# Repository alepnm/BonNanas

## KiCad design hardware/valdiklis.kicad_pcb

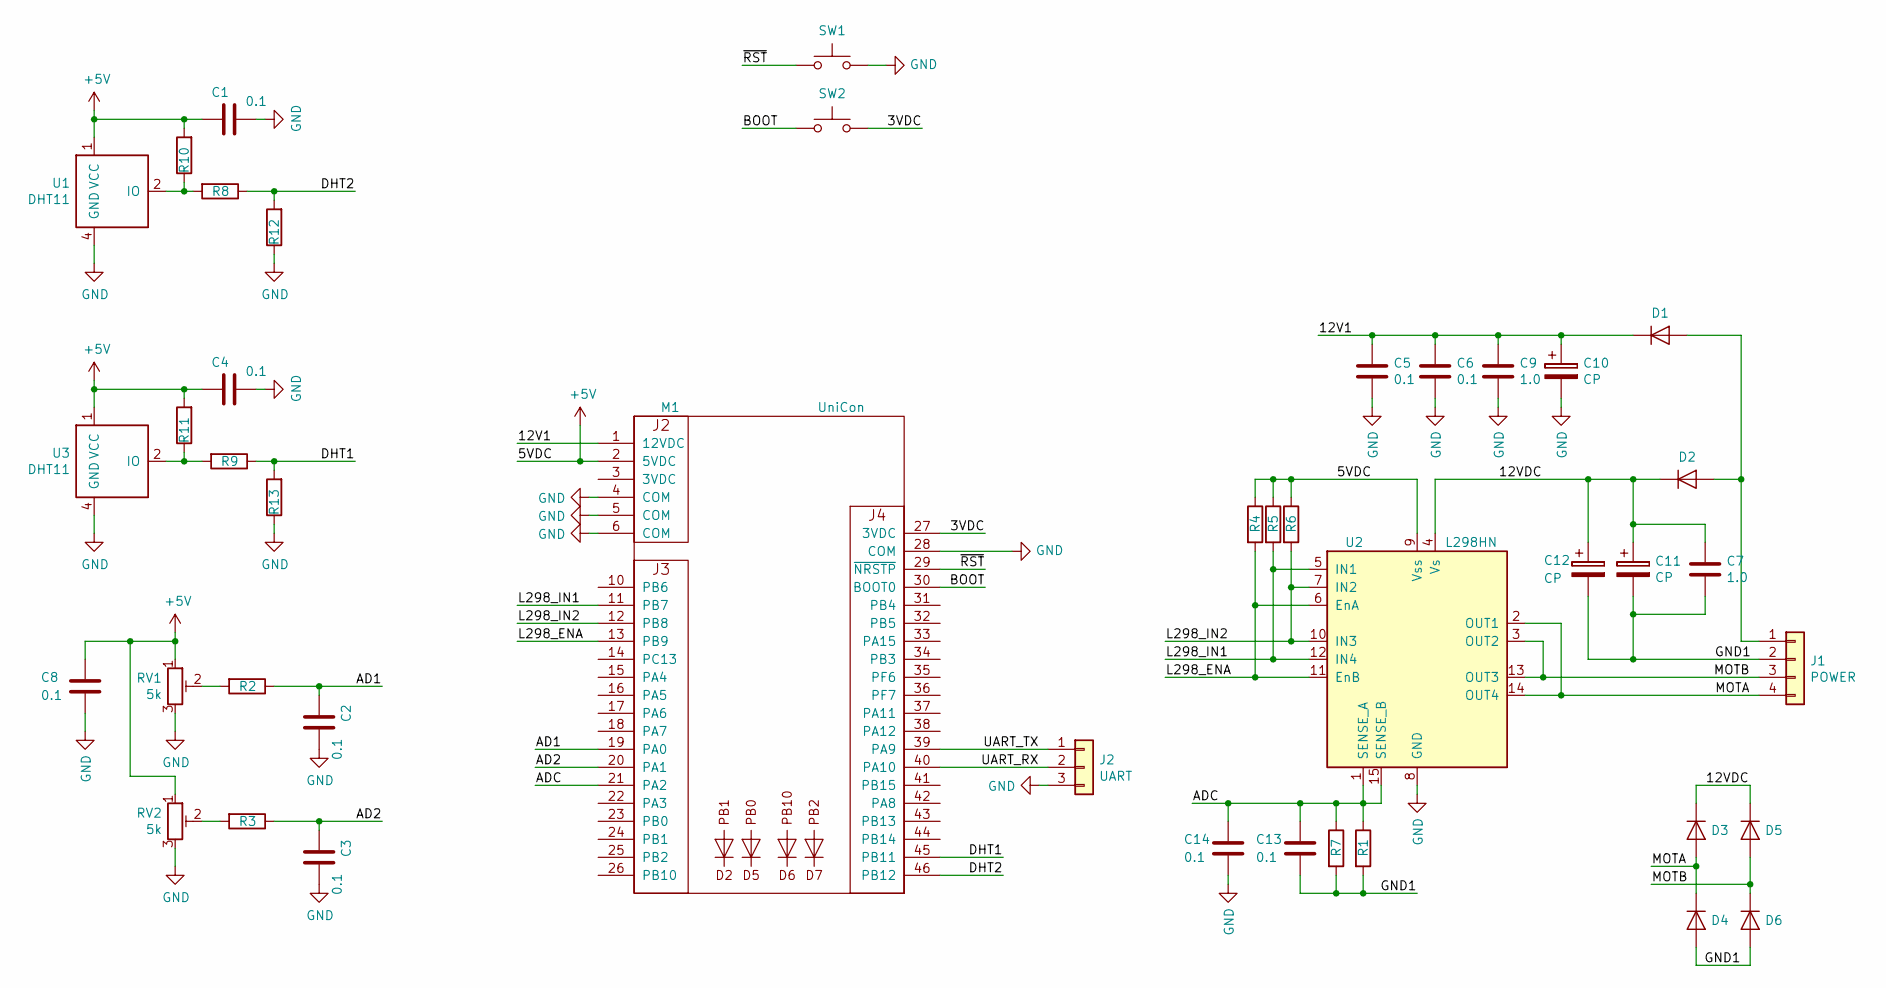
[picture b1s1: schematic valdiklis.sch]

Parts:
C1, C2, C3, C4, C8, C13, C14: 0.1; C_1206_3216Metric
C5, C6: 0.1; C_0805_2012Metric
C7, C9: 1.0; C_1206_3216Metric
C10: CP; CP_Radial_D5.0mm_P2.50mm
C11, C12: CP; CP_Radial_D10.0mm_P5.00mm
D1: D; D_MELF
D2: D; D_DO-27_P15.24mm_Horizontal
D3, D4, D5, D6: D; D_SMA
J1: POWER; PhoenixContact_MSTBA_2,5_4-G-5,08_1x04_P5.08mm_Horizontal
J2: UART; PinHeader_1x03_P2.54mm_Vertical
M1: UniCon; unicon
R1, R7: 1R0; R_Axial_DIN0207_L6.3mm_D2.5mm_P10.16mm_Horizontal
R2, R3, R4, R5, R6: 10k; R_0805_2012Metric
R8, R9: 47R; R_0805_2012Metric
R10, R11, R12, R13: 4,7k; R_0805_2012Metric
RV1, RV2: 5k; Potentiometer_Piher_PT-6-V_Vertical
SW1, SW2: RESET; SW_PUSH_6mm_H5mm
U1, U3: DHT11
U2: L298HN; TO-220-15_P2.54x2.54mm_StaggerOdd_Lead4.58mm_Vertical

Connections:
+5V: C1.2, C4.2, C8.1, M1.2 (5VDC), R4.1, R5.1, R6.1, R10.2, R11.2, RV1.1, RV2.1, U1.1 (VCC), U2.9 (Vss), U3.1 (VCC)
/3VDC: M1.27 (3VDC), SW2.2
/12V1: C5.1, C6.1, C9.1, C10.1, D1.1 (K), M1.1 (12VDC)
/12VDC: C7.1, C11.1, C12.1, D2.1 (K), D3.1 (K), D5.1 (K), U2.4 (Vs)
/AD1: C2.2, M1.19 (PA0), R2.1
/AD2: C3.2, M1.20 (PA1), R3.1
/ADC: C13.1, C14.1, M1.21 (PA2), R1.1, R7.1, U2.1 (SENSE_A), U2.15 (SENSE_B)
/BOOT: M1.30 (BOOT0), SW2.1
/DHT1: M1.45 (PB11), R9.1, R13.2
/DHT2: M1.46 (PB12), R8.1, R12.2
/GND1: C7.2, C11.2, C12.2, C13.2, D4.2 (A), D6.2 (A), J1.2, R1.2, R7.2
/L298_ENA: M1.13 (PB9), R4.2, U2.6 (EnA), U2.11 (EnB)
/L298_IN1: M1.11 (PB7), R5.2, U2.5 (IN1), U2.12 (IN4)
/L298_IN2: M1.12 (PB8), R6.2, U2.7 (IN2), U2.10 (IN3)
/MOTA: D3.2 (A), D4.1 (K), J1.4, U2.2 (OUT1), U2.14 (OUT4)
/MOTB: D5.2 (A), D6.1 (K), J1.3, U2.3 (OUT2), U2.13 (OUT3)
/UART_RX: J2.2, M1.40 (PA10)
/UART_TX: J2.1, M1.39 (PA9)
/~RST: M1.29 (~NRSTP), SW1.1
GND: C1.1, C2.1, C3.1, C4.1, C5.2, C6.2, C8.2, C9.2, C10.2, C14.2, J2.3, M1.4 (COM), M1.5 (COM), M1.6 (COM), M1.28 (COM), R12.1, R13.1, RV1.3, RV2.3, SW1.2, U1.4 (GND), U2.8 (GND), U3.4 (GND)
unnamed: D1.2 (A), D2.2 (A), J1.1
unnamed: R2.2, RV1.2
unnamed: R3.2, RV2.2
unnamed: R8.2, R10.1, U1.2 (IO)
unnamed: R9.2, R11.1, U3.2 (IO)

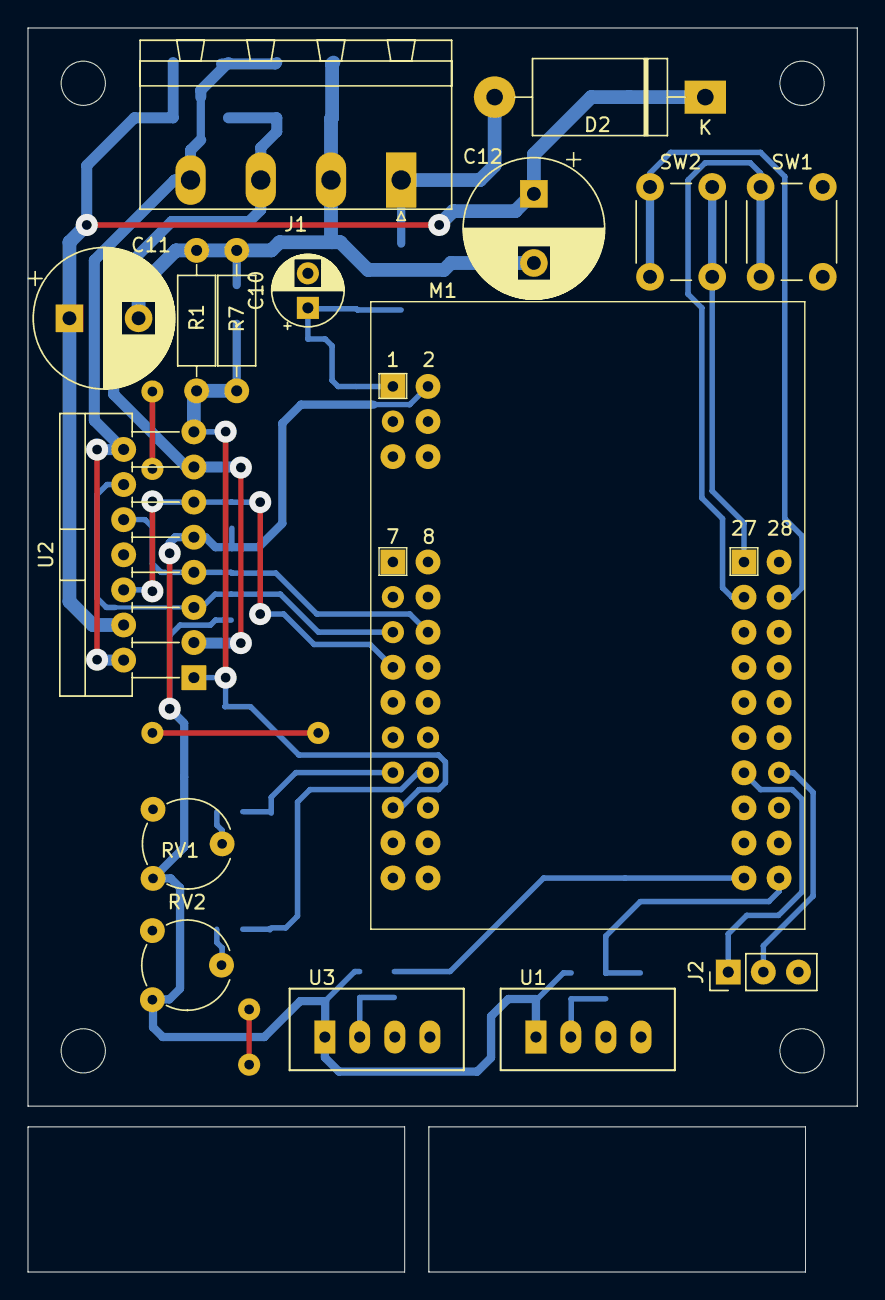
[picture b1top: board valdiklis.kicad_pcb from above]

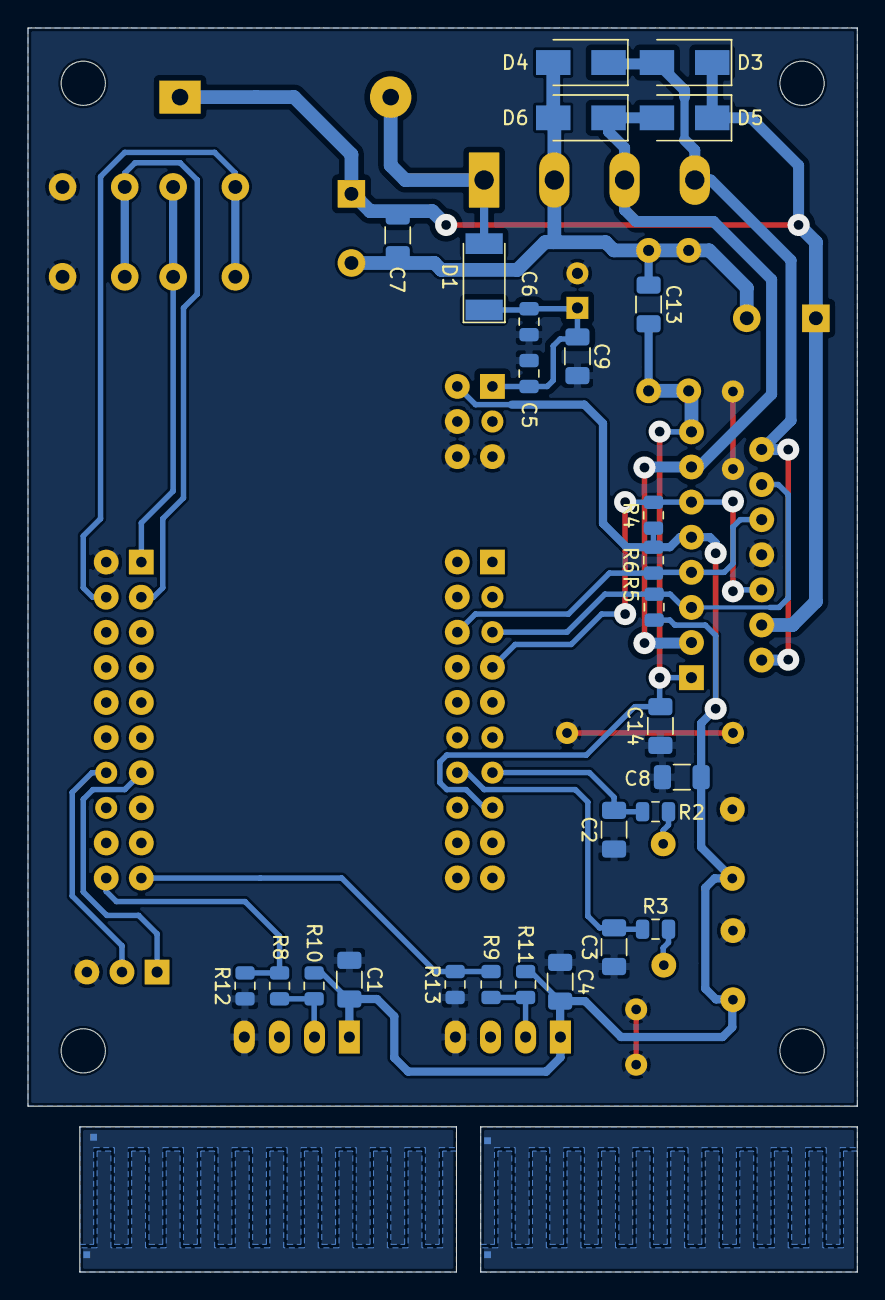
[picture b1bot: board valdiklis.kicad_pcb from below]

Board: 2 copper layers, 60.0 x 90.0 mm, 43 parts (27 on the bottom side), 25 nets.

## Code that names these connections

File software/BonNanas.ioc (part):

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Mcu.Name=STM32F051C8Tx
Mcu.Package=LQFP48
Mcu.UserName=STM32F051C8Tx
PA0.GPIOParameters=GPIO_Label
PA0.GPIO_Label=AD1
PA0.Mode=IN0
PA0.Signal=ADC_IN0
PA1.GPIOParameters=GPIO_Label
PA1.GPIO_Label=AD2
PA1.Mode=IN1
PA1.Signal=ADC_IN1
PA10.Mode=Asynchronous
PA10.Signal=USART1_RX
PA13.Mode=Serial_Wire
PA13.Signal=SYS_SWDIO
PA14.Mode=Serial_Wire
PA14.Signal=SYS_SWCLK
PA2.GPIOParameters=GPIO_Label
PA2.GPIO_Label=ADC
PA2.Mode=IN2
PA2.Signal=ADC_IN2
PA5.GPIOParameters=GPIO_Label
PA5.GPIO_Label=HUMIDITY
PA5.Mode=IN5
PA5.Signal=ADC_IN5
PA9.Mode=Asynchronous
PA9.Signal=USART1_TX
PB0.GPIOParameters=GPIO_Label
PB0.GPIO_Label=LED5
PB0.Signal=GPIO_Output
PB1.GPIOParameters=GPIO_Label
PB1.GPIO_Label=LED2
PB1.Signal=GPIO_Output
PB10.GPIOParameters=GPIO_Label
PB10.GPIO_Label=LED6
PB10.Signal=GPIO_Output
PB11.Signal=GPIO_Analog
PB12.GPIOParameters=GPIO_Speed,GPIO_ModeDefaultOutputPP
PB12.GPIO_ModeDefaultOutputPP=GPIO_MODE_OUTPUT_OD
PB12.GPIO_Speed=GPIO_SPEED_FREQ_MEDIUM
PB12.Signal=GPIO_Output
PB2.GPIOParameters=GPIO_Label
PB2.GPIO_Label=LED7
PB2.Signal=GPIO_Output
PB7.GPIOParameters=GPIO_Label,GPIO_ModeDefaultOutputPP
PB7.GPIO_Label=L298_IN1
PB7.GPIO_ModeDefaultOutputPP=GPIO_MODE_OUTPUT_OD
PB7.Signal=GPIO_Output
PB8.GPIOParameters=GPIO_ModeDefaultPP,GPIO_Label
PB8.GPIO_Label=L298_IN2
PB8.GPIO_ModeDefaultPP=GPIO_MODE_AF_OD
PB8.Signal=S_TIM16_CH1
PB9.GPIOParameters=GPIO_Label
PB9.GPIO_Label=L298_ENA
PB9.Signal=GPIO_Output
RCC.SYSCLKFreq_VALUE=48000000
RCC.SYSCLKSource=RCC_SYSCLKSOURCE_PLLCLK
board=unicon

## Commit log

2019-04-14 repo inicializavimas
2019-04-14 tarpinis kommitas
2019-04-15 pcb plokstes ir schemos paruosimas
2019-04-15 pcb ir schemos paruosimas
2019-04-16 2019-04-16
2019-04-16 2019-04-17
2019-04-22 versija 20190423. pilnai veikiantis softas
2019-04-22 kainorastis
2019-04-23 surenkti reikalingi failai
2019-04-24 kodo optimizavimas. versija 1.0
2019-04-25 versija 1.1-20190425
    papildytas AT komandu sarasas
2019-04-25 kodo optimizavimas
2019-04-25 at komandu papildymas
2019-04-26 2019-04-26
2020-06-02 surasyti kommentai
